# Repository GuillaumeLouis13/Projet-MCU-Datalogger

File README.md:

📊 Datalogger MCU Embarqué

Projet créé dans le cadre d'une formation en conception électronique sous KiCad. Ce datalogger est conçu pour enregistrer des données horodatées grâce à une horloge temps réel (RTC) et une mémoire non-volatile (EEPROM).

💡 Description du projet

J'ai réalisé ce projet en complément de mon stage pour approfondir mes compétences en routage PCB et en conception de systèmes embarqués. Le système repose sur un microcontrôleur ATmega328P et intègre les périphériques suivants :
- Microcontrôleur : ATmega328P-AU (Architecture AVR 8-bit), importé sur KiCad depuis une bibliothèque externe.
- Stockage : Mémoire EEPROM I2C (24LC1025) pour la journalisation des données.
- Horloge : RTC (DS1337S) avec sauvegarde pour le suivi temporel, importé sur KiCad depuis une bibliothèque externe.
- Interface : Connecteur ICSP pour la programmation et connecteurs dédiés (I2C, UART, GPIO) pour l'extension.

🛠️ Architecture électronique

Le circuit a été conçu avec une attention particulière sur la gestion du bruit et l'intégrité du signal :
- Routage 2 couches : Utilisation d'un plan de masse solide pour minimiser les interférences électromagnétiques.
- Découplage : Condensateurs placés au plus près des broches d'alimentation du MCU.
- Signalisation : Isolation des lignes sensibles (Quartz 16 MHz) et gestion rigoureuse du bus I2C.

📸 Aperçu du projet

Schema électrique : 

Routage PCB : 

Modèle 3D final :

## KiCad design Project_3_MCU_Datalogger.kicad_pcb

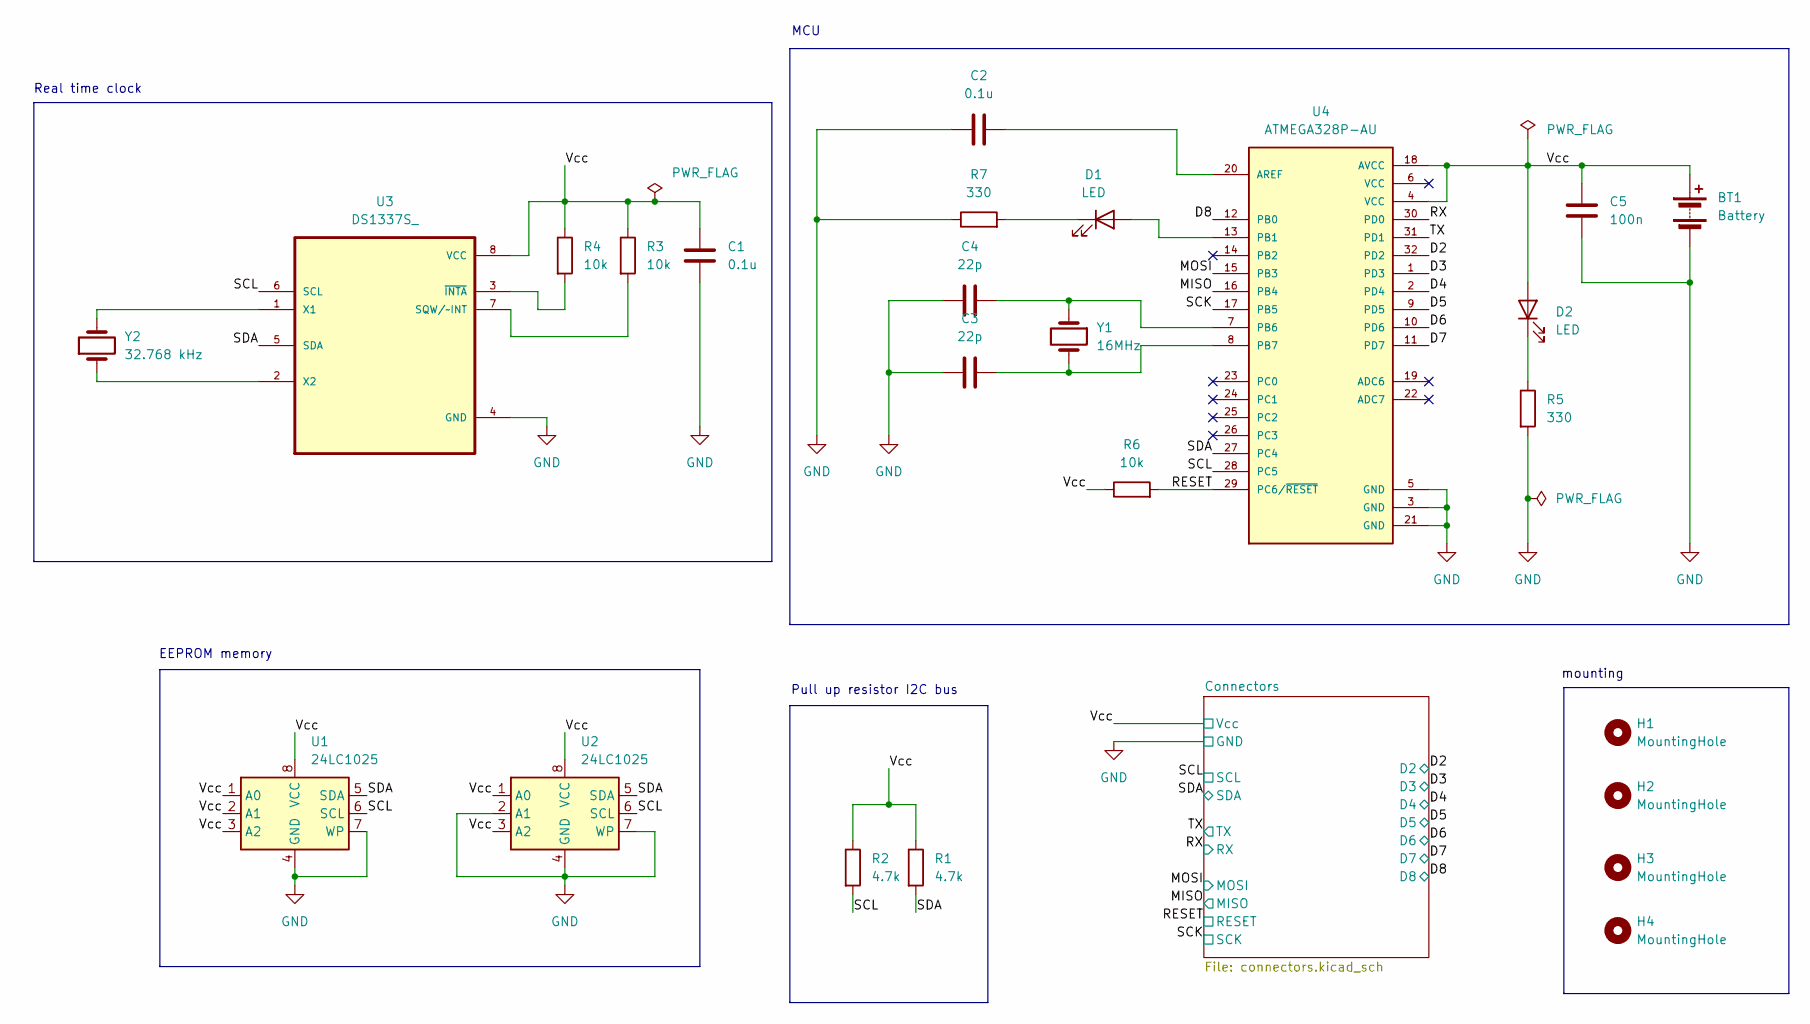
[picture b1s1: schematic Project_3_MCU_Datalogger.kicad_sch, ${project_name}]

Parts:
BT1: Battery; PinHeader_1x02_P2.54mm_Vertical
C1, C2: 0.1u; C_0805_2012Metric
C3, C4: 22p; C_0805_2012Metric
C5: 100n; C_0805_2012Metric
D1, D2: LED; LED_0805_2012Metric
H1, H2, H3, H4: MountingHole; MountingHole_2.1mm
R1, R2: 4.7k; R_0805_2012Metric
R3, R4, R6: 10k; R_0805_2012Metric
R5, R7: 330; R_0805_2012Metric
U1, U2: 24LC1025; SOIC-8_5.3x5.3mm_P1.27mm
U3: DS1337S_; SOIC127P600X175-8N
U4: ATMEGA328P-AU; QFP80P900X900X120-32N; PARTREV 8271A
Y1: 16MHz; Crystal_SMD_5032-2Pin_5.0x3.2mm_HandSoldering
Y2: 32.768 kHz; Crystal_SMD_5032-2Pin_5.0x3.2mm_HandSoldering

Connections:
/D2: U4.32 (PD2); also elsewhere on the board
/D3: U4.1 (PD3); also elsewhere on the board
/D4: U4.2 (PD4); also elsewhere on the board
/D5: U4.9 (PD5); also elsewhere on the board
/D6: U4.10 (PD6); also elsewhere on the board
/D7: U4.11 (PD7); also elsewhere on the board
/D8: U4.12 (PB0); also elsewhere on the board
/MISO: U4.16 (PB4); also elsewhere on the board
/MOSI: U4.15 (PB3); also elsewhere on the board
/RESET: R6.2, U4.29 (PC6/~RESET); also elsewhere on the board
/RX: U4.30 (PD0); also elsewhere on the board
/SCK: U4.17 (PB5); also elsewhere on the board
/SCL: R2.2, U1.6 (SCL), U2.6 (SCL), U3.6 (SCL), U4.28 (PC5); also elsewhere on the board
/SDA: R1.2, U1.5 (SDA), U2.5 (SDA), U3.5 (SDA), U4.27 (PC4); also elsewhere on the board
/TX: U4.31 (PD1); also elsewhere on the board
/Vcc: BT1.1 (+), C1.1, C5.1, D2.2 (A), R1.1, R2.1, R3.1, R4.1, R6.1, U1.1 (A0), U1.2 (A1), U1.3 (A2), U1.8 (VCC), U2.1 (A0), U2.3 (A2), U2.8 (VCC), U3.8 (VCC), U4.4 (VCC), U4.18 (AVCC); also elsewhere on the board
GND: BT1.2 (-), C1.2, C2.1, C3.1, C4.2, C5.2, R5.2, R7.1, U1.4 (GND), U1.7 (WP), U2.2 (A1), U2.4 (GND), U2.7 (WP), U3.4 (GND), U4.3 (GND), U4.5 (GND), U4.21 (GND); also elsewhere on the board
unnamed: D1.2 (A), U4.13 (PB1)
unnamed: D1.1 (K), R7.2
unnamed: D2.1 (K), R5.1
unnamed: R3.2, U3.7 (SQW/~INT)
unnamed: U3.1 (X1), Y2.2
unnamed: U3.2 (X2), Y2.1
unnamed: R4.2, U3.3 (~INTA)
unnamed: C2.2, U4.20 (AREF)
unnamed: C4.1, U4.7 (PB6), Y1.1
unnamed: C3.2, U4.8 (PB7), Y1.2

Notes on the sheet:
Pull up resistor I2C bus
MCU
Real time clock
mounting
EEPROM memory

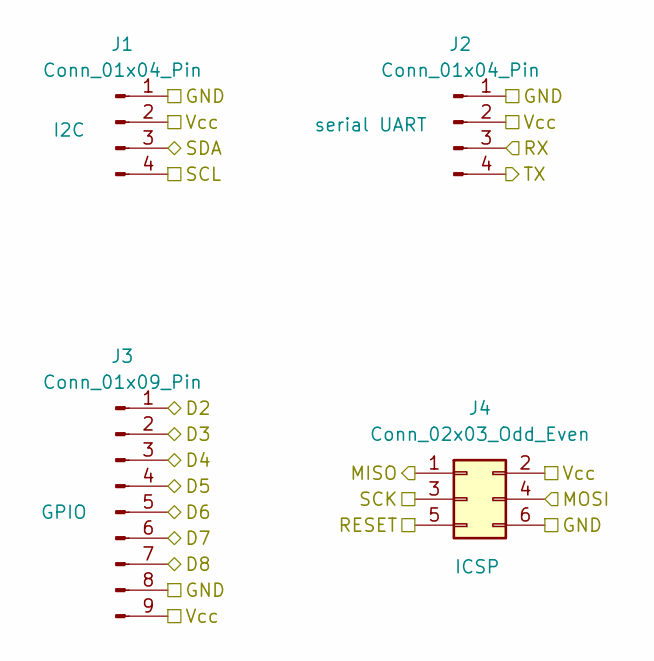
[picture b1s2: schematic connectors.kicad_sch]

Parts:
J1, J2: Conn_01x04_Pin; PinSocket_1x04_P2.54mm_Vertical
J3: Conn_01x09_Pin; PinSocket_1x09_P2.54mm_Vertical
J4: Conn_02x03_Odd_Even; PinSocket_2x03_P2.54mm_Vertical

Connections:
/D2: J3.1; also elsewhere on the board
/D3: J3.2; also elsewhere on the board
/D4: J3.3; also elsewhere on the board
/D5: J3.4; also elsewhere on the board
/D6: J3.5; also elsewhere on the board
/D7: J3.6; also elsewhere on the board
/D8: J3.7; also elsewhere on the board
/MISO: J4.1; also elsewhere on the board
/MOSI: J4.4; also elsewhere on the board
/RESET: J4.5; also elsewhere on the board
/RX: J2.3; also elsewhere on the board
/SCK: J4.3; also elsewhere on the board
/SCL: J1.4; also elsewhere on the board
/SDA: J1.3; also elsewhere on the board
/TX: J2.4; also elsewhere on the board
/Vcc: J1.2, J2.2, J3.9, J4.2; also elsewhere on the board
GND: J1.1, J2.1, J3.8, J4.6; also elsewhere on the board

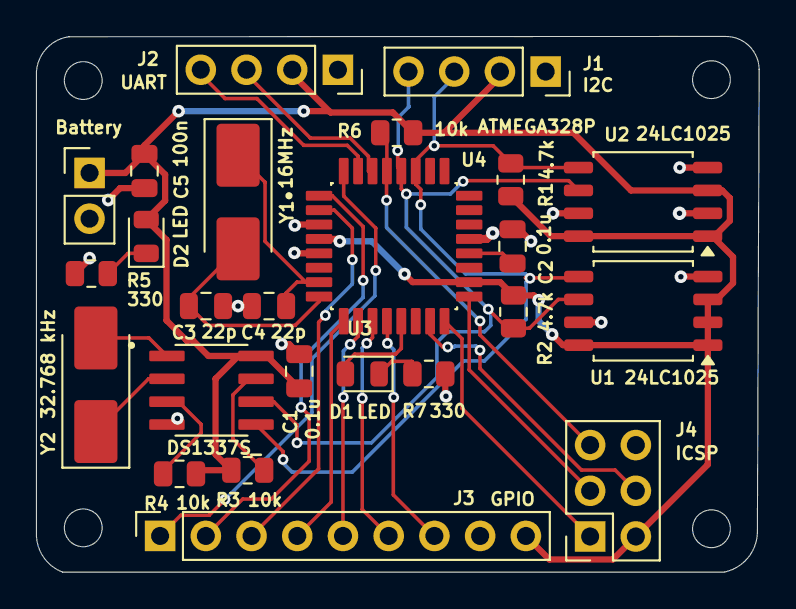
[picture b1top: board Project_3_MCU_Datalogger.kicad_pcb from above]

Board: 2 copper layers, 40.2 x 29.8 mm, 29 parts (0 on the bottom side), 27 nets.

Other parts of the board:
Battery: Battery; PinHeader_1x02_P2.54mm_Vertical

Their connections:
/Vcc: Battery.1 (+); also elsewhere on the board
GND: Battery.2 (-); also elsewhere on the board

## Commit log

2026-05-23 Initial commit : Ajout du projet MCU datalogger KiCad
2026-05-23 Setup of EEschema for MCU project
2026-05-23 Ajout nouveaux fichiers gitignore
2026-05-23 Fix: ignore les fichiers de verrouillage KiCad
2026-05-23 ajout des symboles sur le schéma électrique + import de composants supplémentaires
2026-05-23 stockage des libraries
2026-05-23 Suppression du fichier inutile .DS_store et ajout au gitignore
2026-05-23 Change locations of the components
2026-05-23 ajout des valeurs de composants
2026-05-23 Association des empreintes aux composants
2026-05-23 wiring of sheet 1
2026-05-23 wiring sheet 2, wiring done
2026-05-23 Gesstion des nets classes
2026-05-23 gestion de deux erreurs de footprint librairies
2026-05-23 encadrement des blocs et présentation du circuit
2026-05-23 setup feuille PCB et importation 3D models
2026-05-23 Placement des composants avant routage
2026-05-24 amelioration disposition composants et changements circuit
2026-05-24 Fin du routage sur deux couches et modifications du schema
2026-05-24 Création du readme
2026-05-24 ajout des images du projet
2026-05-24 Rename back 3D model.png to back_3D_model.png
2026-05-24 Rename front 3D model.png to front_3D_model.png
2026-05-24 commit final version 2 layers
2026-05-24 ajout image schema electrique
2026-05-24 Update README.md avec schema électrique
